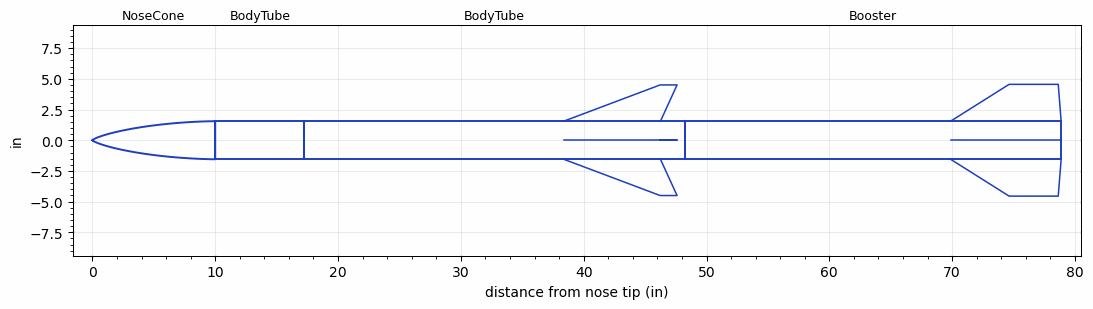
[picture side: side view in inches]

<RASAeroDocument>
 <FileVersion>2</FileVersion>
 <RocketDesign>
  <NoseCone>
   <Length>10</Length>
   <Diameter>3.1</Diameter>
   <Shape>LV-Haack</Shape>
   <Location>0</Location>
  </NoseCone>
  <BodyTube>
   <Length>7.25</Length>
   <Diameter>3.1</Diameter>
   <Location>10</Location>
  </BodyTube>
  <BodyTube>
   <Length>31</Length>
   <Diameter>3.1</Diameter>
   <Location>17.25</Location>
   <Fin>
    <Count>4</Count>
    <Chord>7.874</Chord>
    <Span>2.953</Span>
    <SweepDistance>7.8474</SweepDistance>
    <TipChord>1.378</TipChord>
    <Thickness>0.25</Thickness>
    <Location>9.874001</Location>
    <AirfoilSection>Square</AirfoilSection>
   </Fin>
  </BodyTube>
  <Booster>
   <Length>30.62205</Length>
   <Diameter>3.1</Diameter>
   <InsideDiameter>3.1</InsideDiameter>
   <Location>48.25</Location>
   <ShoulderLength>0</ShoulderLength>
   <Fin>
    <Count>4</Count>
    <Chord>9</Chord>
    <Span>3</Span>
    <SweepDistance>4.76314</SweepDistance>
    <TipChord>4</TipChord>
    <Thickness>0.25</Thickness>
    <Location>9</Location>
    <AirfoilSection>Square</AirfoilSection>
   </Fin>
  </Booster>
  <Surface>Smooth (Zero Roughness)</Surface>
  <ModifiedBarrowman>False</ModifiedBarrowman>
  <Turbulence>False</Turbulence>
  <UseBooster1>False</UseBooster1>
  <UseBooster2>False</UseBooster2>
 </RocketDesign>
 <LaunchSite>
  <Altitude>2000</Altitude>
  <Pressure>0</Pressure>
  <RodAngle>0</RodAngle>
  <RodLength>20</RodLength>
  <Temperature>70</Temperature>
  <WindSpeed>15</WindSpeed>
 </LaunchSite>
 <Recovery>
  <Altitude1>1000</Altitude1>
  <Altitude2>1000</Altitude2>
  <DeviceType1>None</DeviceType1>
  <DeviceType2>None</DeviceType2>
  <Event1>False</Event1>
  <Event2>False</Event2>
  <Size1>1</Size1>
  <Size2>1</Size2>
  <EventType1>None</EventType1>
  <EventType2>None</EventType2>
  <CD1>1.33</CD1>
  <CD2>1.33</CD2>
 </Recovery>
 <SimulationList>
  <Simulation>
   <SustainerEngine>J244-WH-14A  (CTI)</SustainerEngine>
   <SustainerLaunchWt>7.58</SustainerLaunchWt>
   <SustainerNozzleDiameter>1.181</SustainerNozzleDiameter>
   <SustainerCG>28.58</SustainerCG>
   <SustainerIgnitionDelay>0.5</SustainerIgnitionDelay>
   <Booster1Engine>J430-WT-18A  (CTI)</Booster1Engine>
   <Booster1LaunchWt>12.98</Booster1LaunchWt>
   <Booster1SeparationDelay>0</Booster1SeparationDelay>
   <Booster1IgnitionDelay>0</Booster1IgnitionDelay>
   <Booster1CG>44.88</Booster1CG>
   <Booster1NozzleDiameter>1.181</Booster1NozzleDiameter>
   <IncludeBooster1>True</IncludeBooster1>
   <Booster2Delay>0</Booster2Delay>
   <IncludeBooster2>False</IncludeBooster2>
   <TimetoApogee>20.34032</TimetoApogee>
   <MaxAltitude>7152.604</MaxAltitude>
   <MaxVelocity>867.5497</MaxVelocity>
  </Simulation>
 </SimulationList>
</RASAeroDocument>
